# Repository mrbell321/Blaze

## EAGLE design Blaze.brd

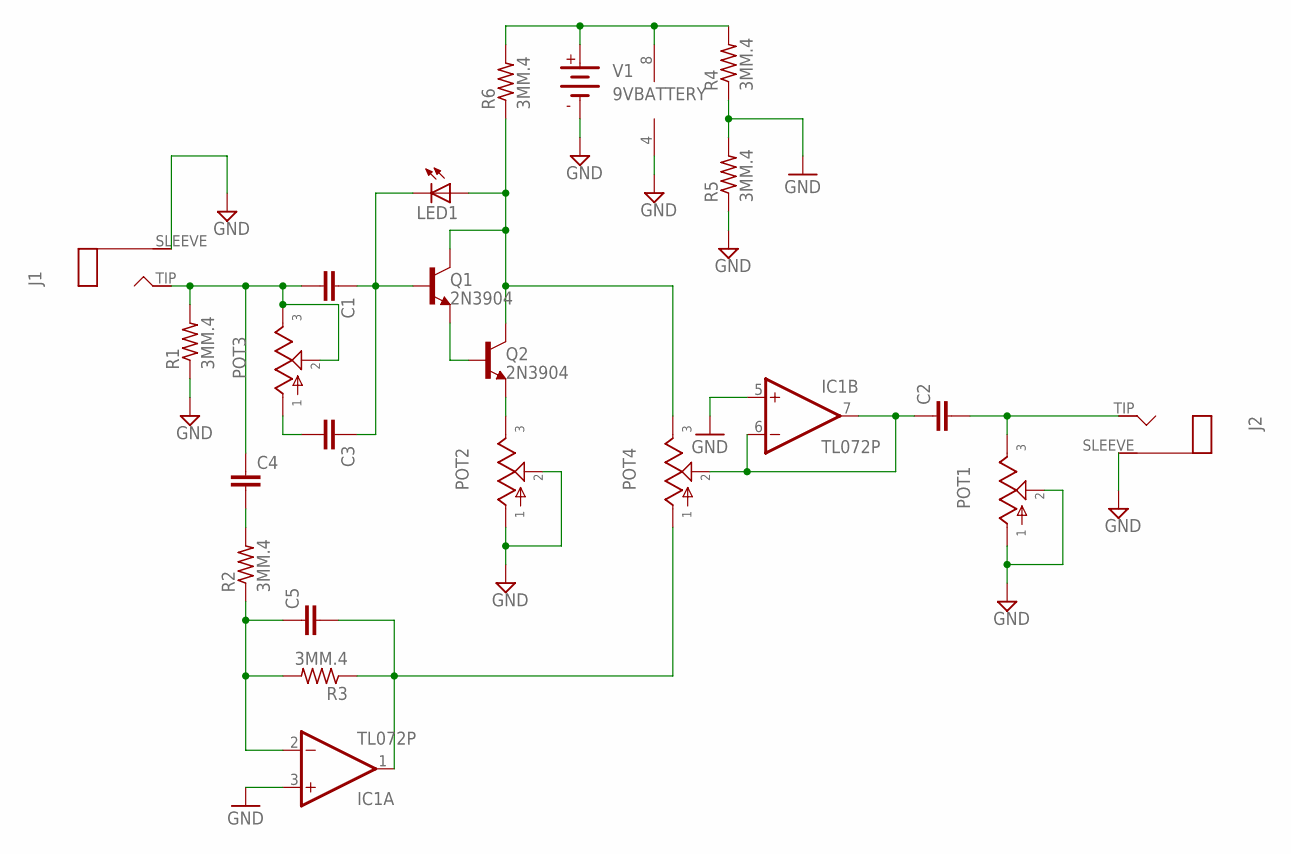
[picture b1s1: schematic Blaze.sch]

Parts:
C1, C2, C3, C4, C5: 050X030_0251; 050X030_025
IC1: TL072P; DIL08
J1, J2: MONOA; MONO_JACK_A
LED1: LED5MM
POT1, POT2, POT3, POT4: POT
Q1, Q2: 2N3904; TO92-
R1, R2, R3, R4, R5, R6: 3MM.4; R0204/4
V1: 9VBATTERY; AB9V

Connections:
GND: IC1.3 (+IN), IC1.4 (V-), IC1.5 (+IN), J1.SLEEVE, J2.SLEEVE, POT1.1, POT1.2, POT2.1, POT2.2, R1.1, R4.1, R5.1, R5.2, V1.-
unnamed: C1.2, C4.1, J1.TIP, POT3.2, POT3.3, R1.2
unnamed: C1.1, C3.1, LED1.K (C), Q1.2 (B)
unnamed: Q1.3 (E), Q2.2 (B)
unnamed: LED1.A, POT4.3, Q1.1 (C), Q2.1 (C), R6.1
unnamed: POT2.3, Q2.3 (E)
unnamed: C2.2, J2.TIP, POT1.3
unnamed: IC1.8 (V+), R4.2, R6.2, V1.+
unnamed: C3.2, POT3.1
unnamed: C2.1, IC1.6 (-IN), IC1.7 (OUT), POT4.2
unnamed: C5.2, IC1.1 (OUT), POT4.1, R3.1
unnamed: C4.2, R2.2
unnamed: C5.1, IC1.2 (-IN), R2.1, R3.2

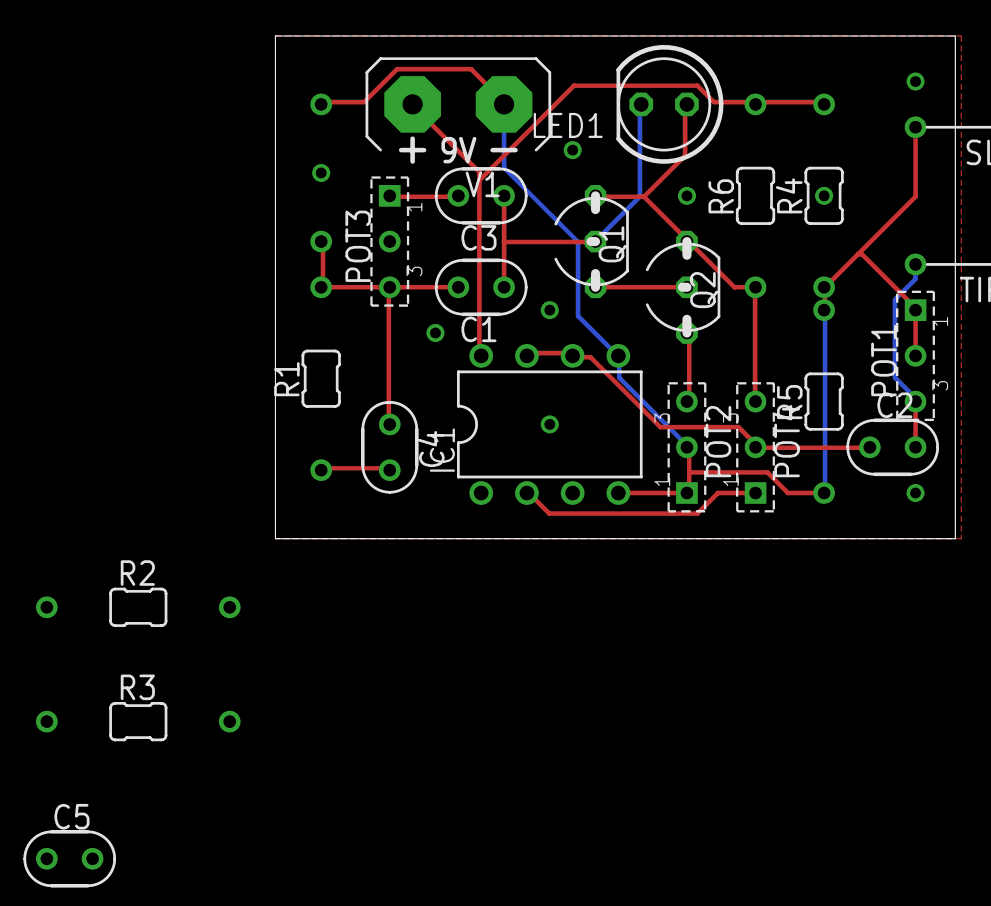
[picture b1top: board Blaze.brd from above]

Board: 2 copper layers, 37.8 x 27.9 mm, 22 parts (1 on the bottom side), 13 nets.
